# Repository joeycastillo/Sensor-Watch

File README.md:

The Sensor Watch
================

The [Sensor Watch](https://www.sensorwatch.net) is a board replacement for the classic Casio F-91W wristwatch. It is powered by a Microchip SAM L22 microcontroller with built-in segment LCD controller. You can write your own programs for the watch using the provided watch library, program the watch over USB using the built-in UF2 bootloader, and then install the board in your existing watch case to run your own software on your wrist.

Features:
* ARM Cortex M0+ microcontroller
* 32KHz crystal for real-time clock with alarm function
* Ten digit segment LCD, plus five indicator segments
* Three interrupt capable buttons
* Red / green PWM’able LED backlight
* Optional piezo buzzer (requires some light soldering)
* On-board USB Micro B connector
* Reset button with double-tap UF2 bootloader
* Nine-pin flex PCB connector

You may have noticed that there are no sensors on this board. That is by design: rather than pick sensors for you, the goal is to add a tiny flexible PCB with the sensors YOU want, and interface them over the nine-pin connector. The connector provides the following options for power and connectivity:

* 3V power (nominal voltage from a CR2016 coin cell, can drop to ~2.7V)
* An I²C interface with built-in pull-up resistors
* Five general purpose IO pins, which can be configured as:
    * Five analog inputs
    * Five interrupt-capable digital inputs, with internal pull-up or pull-down resistors
    * Five digital outputs
    * SPI controller (with one spare analog / GPIO pin leftover)
    * One UART TX/RX pair (with three GPIO leftover)
    * Up to four PWM pins on two independent TC instances
    * Two external wake inputs that can wake from the ultra-low-power BACKUP mode

| **Pin** | **Digital** | **Interrupt**   | **Analog**    | **I2C**             | **SPI**              | **UART**                 | **PWM**  | **Ext. Wake** |
| :-----: | :---------: | :-------------: | :-----------: | :-----------------: | :------------------: | :----------------------: | :------: | :-----------: |
| **A0**  | PB04        | EIC/EXTINT\[4\] | ADC/AIN\[12\] | —                   | —                    | —                        | —        | —             |
| **SCL** | —           | —               | —             | SCL<br>SERCOM1\[1\] | —                    | —                        | —        | —             |
| **SDA** | —           | —               | —             | SDA<br>SERCOM1\[0\] | —                    | —                        | —        | —             |
| **A1**  | PB01        | EIC/EXTINT\[1\] | ADC/AIN\[9\]  | —                   | SCK<br>SERCOM3\[3\]  | RX<br>SERCOM3\[3\]       | TC3\[1\] | —             |
| **A2**  | PB02        | EIC/EXTINT\[2\] | ADC/AIN\[10\] | —                   | MOSI<br>SERCOM3\[0\] | TX or RX<br>SERCOM3\[0\] | TC2\[0\] | RTC/IN\[1\]   |
| **A3**  | PB03        | EIC/EXTINT\[3\] | ADC/AIN\[11\] | —                   | CS<br>SERCOM3\[1\]   | RX<br>SERCOM3\[1\]       | TC2\[1\] | —             |
| **A4**  | PB00        | EIC/EXTINT\[0\] | ADC/AIN\[8\]  | —                   | MISO<br>SERCOM3\[2\] | TX or RX<br>SERCOM3\[2\] | TC3\[0\] | RTC/IN\[0\]   |

These tiny “sensor boards” have a set outline, and the available area for your electronics is quite small (5.7 × 5.7 × 1 mm). Still, this is plenty of room for an environmental sensor, MEMS accelerometer or magnetometer and a couple of decoupling capacitors. Note that you will likely be limited to QFN and LGA type parts; SOICs are too large, and even SSOP packages are generally too thick. You can find reference designs for several sensor boards in the `PCB/Sensor Boards` directory within this repository.

Getting code on the watch
-------------------------
The watch library in this repository is very work-in-progress, but it should allow you to get started. To create a new project, copy the “starter-project” folder in the apps folder, and write your code in the app.c file.

You will need to install [the GNU Arm Embedded Toolchain](https://developer.arm.com/tools-and-software/open-source-software/developer-tools/gnu-toolchain/gnu-rm/downloads/) to build projects for the watch. The watch library has been tested with the `9-2019-q4-major` version and the `10.3-2021.07` versions. If you're using Debian or Ubuntu, it should be sufficient to `apt install gcc-arm-none-eabi`.

To build your project, open your terminal and navigate to the project's `make` folder, then type `make`.

To install the project onto your Sensor Watch board, plug the watch into your USB port and double tap the tiny Reset button on the back of the board. You should see the LED light up red and begin pulsing. (If it does not, make sure you didn’t plug the board in upside down). Once you see the “WATCHBOOT” drive appear on your desktop, type `make install`. This will convert your compiled program to a UF2 file, and copy it over to the watch.

Using the Movement framework
----------------------------
If you just want to make minor modifications and use existing code, start with the `movement` directory. You can build the default watch firmware with:

```
cd movement/make
make
```

Then copy `movement/make/build/watch.uf2` to your watch. If you'd like to modify which faces are built, see `movement_config.h`.

You may want to test out changes in the emulator first. To do this, you'll need to install [emscripten](https://emscripten.org/), then run:

```
cd movement/make
emmake make
python3 -m http.server -d build-sim
```

Finally, visit [watch.html](http://localhost:8000/watch.html) to see your work.

Hardware Schematics and PCBs
----------------------------

| Name | Color | Schematic | Gerbers |
| ---- | ----- | --------- | ------- |
| Sensorwatch Lite | RED   | [PCB/Main Boards/OSO-SWAT-B1](PCB/Main%20Boards/OSO-SWAT-B1) | [OSO-SWAT-B1-03](PCB/Main%20Boards/OSO-SWAT-B1/OSO-SWAT-B1-03.zip) |
| Sensorwatch      | GREEN | [OSO-SWAT-A1-05](PCB/Main%20Boards/OSO-SWAT-A1/OSO-SWAT-A1-05.sch) (Eagle format) | ? |
| Sensorwatch Pro  | TBD   | TBD  | TBD |

License
-------
Different components of the project are licensed differently, see [LICENSE.md](https://github.com/joeycastillo/Sensor-Watch/blob/main/LICENSE.md).

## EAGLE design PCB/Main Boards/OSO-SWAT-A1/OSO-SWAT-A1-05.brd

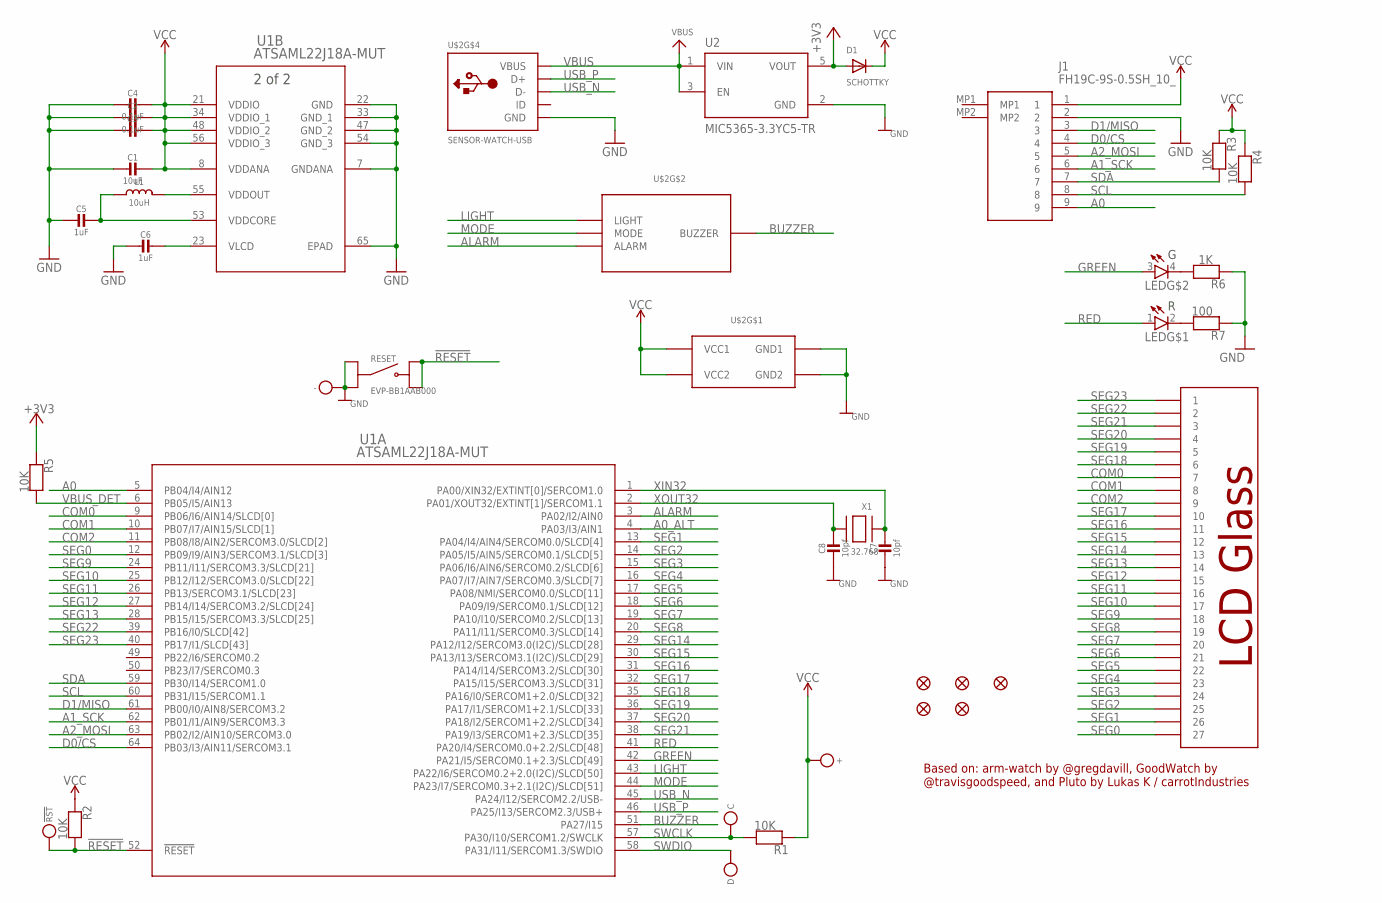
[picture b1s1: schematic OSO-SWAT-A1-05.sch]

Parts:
!RST: MICROBUILDER_TESTPOINTROUND1.5MM; MICROBUILDER_TESTPOINT_ROUND_1.5MM
+: MICROBUILDER_TESTPOINTROUND1.5MM; MICROBUILDER_TESTPOINT_ROUND_1.5MM
-: MICROBUILDER_TESTPOINTROUND1.5MM; MICROBUILDER_TESTPOINT_ROUND_1.5MM
C: MICROBUILDER_TESTPOINTROUND1.5MM; MICROBUILDER_TESTPOINT_ROUND_1.5MM
C1: 10uF; _0603MP
C2, C3, C4: 0.1uF; _0603MP
C5, C6: 1uF; _0603MP
C7, C8: 10pf; _0402MP
D: MICROBUILDER_TESTPOINTROUND1.5MM; MICROBUILDER_TESTPOINT_ROUND_1.5MM
D1: SCHOTTKY; SOD-323F
FID1, FID2, FID3, FID4, FID6: FIDUCIAL_1MM
J1: FH19C-9S-0.5SH_10_; FH19C9S05SH10
L1: 10uH; MICROBUILDER__0805MP
LED: QBLP655-RIG; LED_QBLP655
R1, R2, R3, R4, R5: 10K; _0603MP
R6: 1K; _0603MP
R7: 100; _0603MP
RESET: EVP-BB1AAB000; SW_EVP-BB1AAB000
U1: ATSAML22J18A-MUT; QFN64_9X9MC_MCH
U2: MIC5365-3.3YC5-TR; SOT65P210X110-5N
U$2: SENSOR-WATCH-USB; CASIO-F91W-OUTLINE-USB
X1: 32.768; XTAL3215

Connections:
!RESET: !RST.P$1, R2.2, RESET.B1, RESET.B2, U1.52 (!RESET)
+3V3: D1.A, R5.1, U2.5 (VOUT)
A0: J1.9, U1.5 (PB04/I4/AIN12)
A0_ALT: U1.4 (PA03/I3/AIN1)
A1_SCK: J1.6, U1.62 (PB01/I1/AIN9/SERCOM3.3)
A2_MOSI: J1.5, U1.63 (PB02/I2/AIN10/SERCOM3.0)
ALARM: U1.3 (PA02/I2/AIN0), U$2.ALARM
BUZZER: U1.51 (PA27/I15), U$2.BUZZER
COM0: U1.9 (PB06/I6/AIN14/SLCD[0]), U$2.7
COM1: U1.10 (PB07/I7/AIN15/SLCD[1]), U$2.8
COM2: U1.11 (PB08/I8/AIN2/SERCOM3.0/SLCD[2]), U$2.9
D0/CS: J1.4, U1.64 (PB03/I3/AIN11/SERCOM3.1)
D1/MISO: J1.3, U1.61 (PB00/I0/AIN8/SERCOM3.2)
GND: -.P$1, C1.2, C2.2, C3.2, C4.2, C5.2, C6.2, C7.2, C8.2, J1.2, R6.1, R7.1, RESET.A1, RESET.A2, U1.7 (GNDANA), U1.22 (GND), U1.33 (GND_1), U1.47 (GND_2), U1.54 (GND_3), U1.65 (EPAD), U2.2 (GND), U$2.GND, U$2.GND1, U$2.GND2
GREEN: LED.3 (A), U1.42 (PA21/I5/SERCOM0.1+2.3/SLCD[49])
LIGHT: U1.43 (PA22/I6/SERCOM0.2+2.0(I2C)/SLCD[50]), U$2.LIGHT
MODE: U1.44 (PA23/I7/SERCOM0.3+2.1(I2C)/SLCD[51]), U$2.MODE
unnamed: LED.4 (C), R6.2
unnamed: LED.2 (C), R7.2
RED: LED.1 (A), U1.41 (PA20/I4/SERCOM0.0+2.2/SLCD[48])
SCL: J1.8, R4.2, U1.60 (PB31/I15/SERCOM1.1)
SDA: J1.7, R3.2, U1.59 (PB30/I14/SERCOM1.0)
SEG0: U1.12 (PB09/I9/AIN3/SERCOM3.1/SLCD[3]), U$2.27
SEG1: U1.13 (PA04/I4/AIN4/SERCOM0.0/SLCD[4]), U$2.26
SEG2: U1.14 (PA05/I5/AIN5/SERCOM0.1/SLCD[5]), U$2.25
SEG3: U1.15 (PA06/I6/AIN6/SERCOM0.2/SLCD[6]), U$2.24
SEG4: U1.16 (PA07/I7/AIN7/SERCOM0.3/SLCD[7]), U$2.23
SEG5: U1.17 (PA08/NMI/SERCOM0.0/SLCD[11]), U$2.22
SEG6: U1.18 (PA09/I9/SERCOM0.1/SLCD[12]), U$2.21
SEG7: U1.19 (PA10/I10/SERCOM0.2/SLCD[13]), U$2.20
SEG8: U1.20 (PA11/I11/SERCOM0.3/SLCD[14]), U$2.19
SEG9: U1.24 (PB11/I11/SERCOM3.3/SLCD[21]), U$2.18
SEG10: U1.25 (PB12/I12/SERCOM3.0/SLCD[22]), U$2.17
SEG11: U1.26 (PB13/SERCOM3.1/SLCD[23]), U$2.16
SEG12: U1.27 (PB14/I14/SERCOM3.2/SLCD[24]), U$2.15
SEG13: U1.28 (PB15/I15/SERCOM3.3/SLCD[25]), U$2.14
SEG14: U1.29 (PA12/I12/SERCOM3.0(I2C)/SLCD[28]), U$2.13
SEG15: U1.30 (PA13/I13/SERCOM3.1(I2C)/SLCD[29]), U$2.12
SEG16: U1.31 (PA14/I14/SERCOM3.2/SLCD[30]), U$2.11
SEG17: U1.32 (PA15/I15/SERCOM3.3/SLCD[31]), U$2.10
SEG18: U1.35 (PA16/I0/SERCOM1+2.0/SLCD[32]), U$2.6
SEG19: U1.36 (PA17/I1/SERCOM1+2.1/SLCD[33]), U$2.5
SEG20: U1.37 (PA18/I2/SERCOM1+2.2/SLCD[34]), U$2.4
SEG21: U1.38 (PA19/I3/SERCOM1+2.3/SLCD[35]), U$2.3
SEG22: U1.39 (PB16/I0/SLCD[42]), U$2.2
SEG23: U1.40 (PB17/I1/SLCD[43]), U$2.1
SWCLK: C.P$1, R1.2, U1.57 (PA30/I10/SERCOM1.2/SWCLK)
SWDIO: D.P$1, U1.58 (PA31/I11/SERCOM1.3/SWDIO)
USB_N: U1.45 (PA24/I12/SERCOM2.2/USB-), U$2.USB_N (D-)
USB_P: U1.46 (PA25/I13/SERCOM2.3/USB+), U$2.USB_P (D+)
VBUS: U2.1 (VIN), U2.3 (EN), U$2.VBUS
VBUS_DET: R5.2, U1.6 (PB05/I5/AIN13)
VCC: +.P$1, C1.1, C2.1, C3.1, C4.1, D1.C, J1.1, R1.1, R2.1, R3.1, R4.1, U1.8 (VDDANA), U1.21 (VDDIO), U1.34 (VDDIO_1), U1.48 (VDDIO_2), U1.56 (VDDIO_3), U$2.VCC1, U$2.VCC2
VDDCORE: C5.1, L1.1, U1.53 (VDDCORE)
VDDOUT: L1.2, U1.55 (VDDOUT)
VLCD: C6.1, U1.23 (VLCD)
XIN32: C7.1, U1.1 (PA00/XIN32/EXTINT[0]/SERCOM1.0), X1.P$1
XOUT32: C8.1, U1.2 (PA01/XOUT32/EXTINT[1]/SERCOM1.1), X1.P$2

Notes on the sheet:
Based on: arm-watch by @gregdavill, GoodWatch by @travisgoodspeed, and Pluto by Lukas K / carrotIndustries

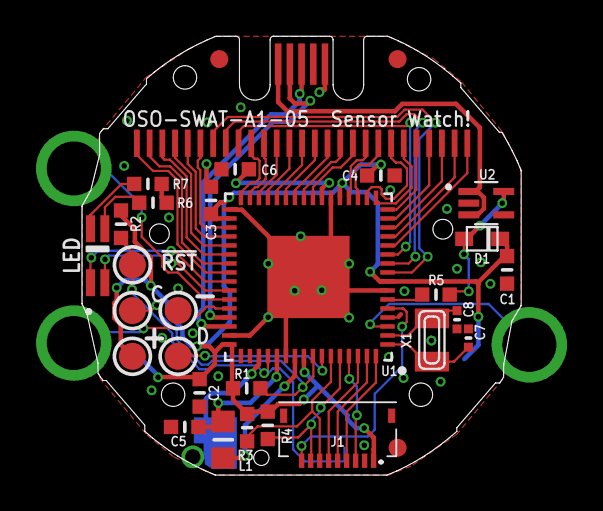
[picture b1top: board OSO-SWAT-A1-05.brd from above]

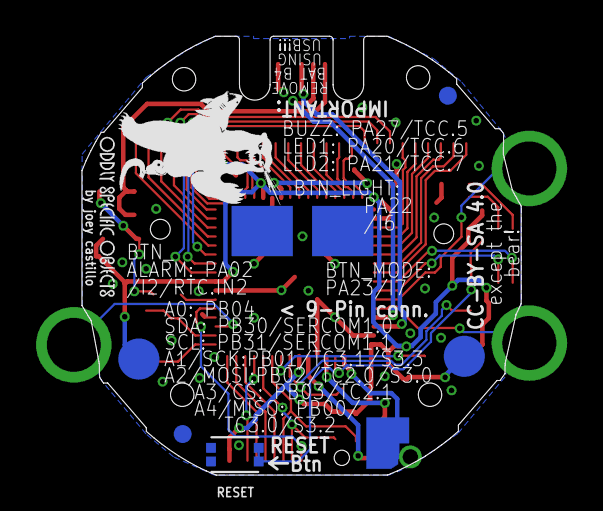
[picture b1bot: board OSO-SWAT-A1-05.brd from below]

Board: 2 copper layers, 24.4 x 24.4 mm, 36 parts (5 on the bottom side), 57 nets.

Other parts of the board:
U$5: OSO_BEAR_250X360MIL_1000DPI
U$6: OSO_WORDMARK_ONELINE_350MIL_1000DPI

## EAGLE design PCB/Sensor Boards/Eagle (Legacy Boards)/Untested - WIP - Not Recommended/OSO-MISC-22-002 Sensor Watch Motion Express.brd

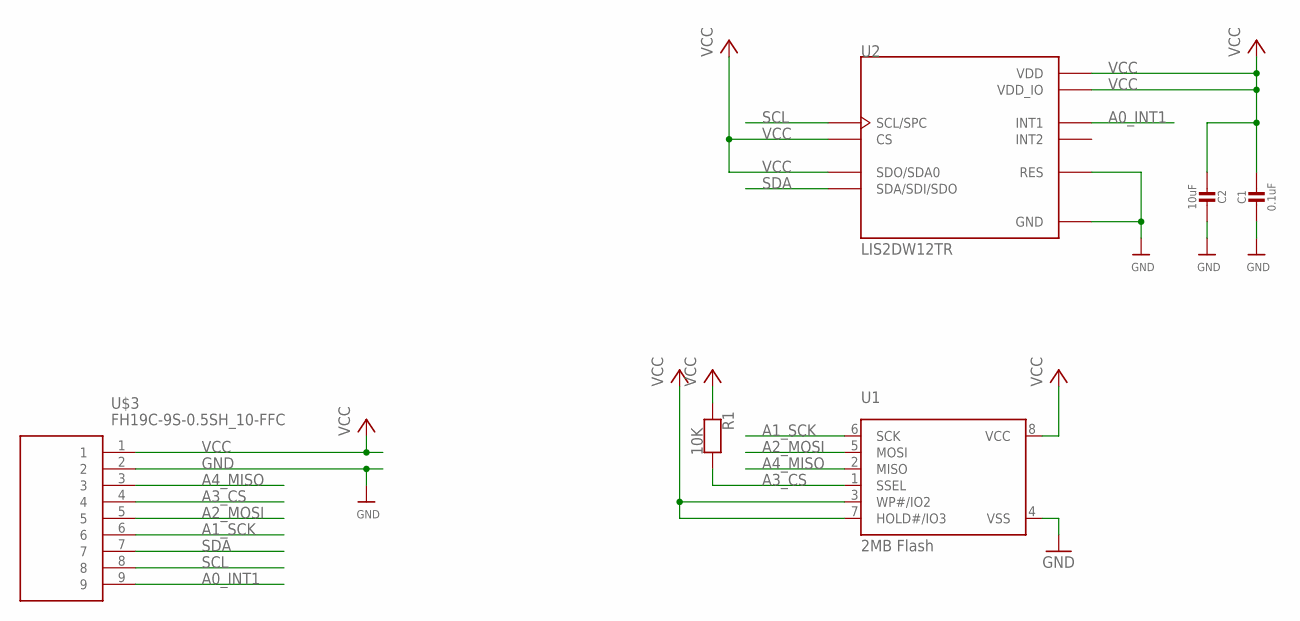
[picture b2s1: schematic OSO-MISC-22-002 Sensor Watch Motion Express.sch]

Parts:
C1: 0.1uF; _0603MP
C2: 10uF; _0603MP
R1: 10K; _0603MP
U1: 2MB Flash; USON8
U2: LIS2DW12TR; LGA12R50P4X4_200X200X70
U$3: FH19C-9S-0.5SH_10-FFC; FH19C9S05SH10-FFC

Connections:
A0_INT1: U2.12 (INT1), U$3.9
A1_SCK: U1.6 (SCK), U$3.6
A2_MOSI: U1.5 (MOSI), U$3.5
A3_CS: R1.2, U1.1 (SSEL), U$3.4
A4_MISO: U1.2 (MISO), U$3.3
GND: C1.2, C2.1, U1.4 (VSS), U2.6 (GND), U2.7 (RES), U2.8 (GND), U$3.2
SCL: U2.1 (SCL/SPC), U$3.8
SDA: U2.4 (SDA/SDI/SDO), U$3.7
VCC: C1.1, C2.2, R1.1, U1.3 (WP#/IO2), U1.7 (HOLD#/IO3), U1.8 (VCC), U2.2 (CS), U2.3 (SDO/SDA0), U2.9 (VDD), U2.10 (VDD_IO), U$3.1

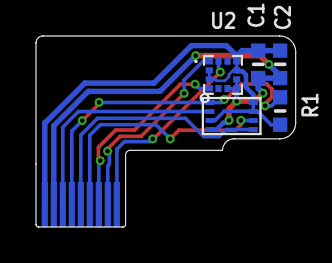
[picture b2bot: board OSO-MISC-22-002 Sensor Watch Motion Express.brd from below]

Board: 2 copper layers, 14.4 x 10.6 mm, 6 parts (5 on the bottom side), 9 nets.

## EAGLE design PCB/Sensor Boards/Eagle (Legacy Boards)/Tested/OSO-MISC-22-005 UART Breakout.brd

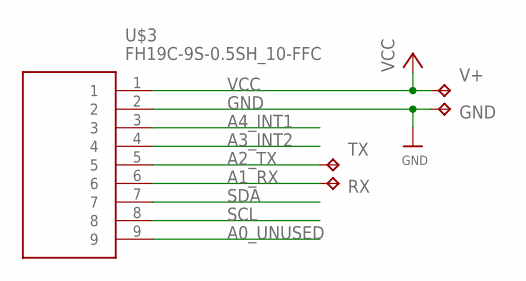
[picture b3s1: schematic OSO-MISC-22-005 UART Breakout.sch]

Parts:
GND: TPTP20R; TP20R
RX: TPTP20R; TP20R
TX: TPTP20R; TP20R
U$3: FH19C-9S-0.5SH_10-FFC; FH19C9S05SH10-FFC
V+: TPTP20R; TP20R

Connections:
A0_UNUSED: U$3.9
A1_RX: RX.TP, U$3.6
A2_TX: TX.TP, U$3.5
A3_INT2: U$3.4
A4_INT1: U$3.3
GND: GND.TP, U$3.2
SCL: U$3.8
SDA: U$3.7
VCC: U$3.1, V+.TP

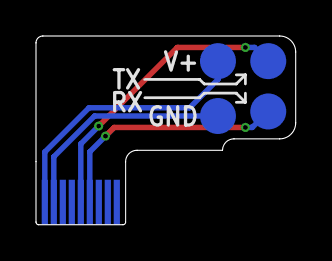
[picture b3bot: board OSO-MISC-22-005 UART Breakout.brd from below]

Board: 2 copper layers, 14.4 x 10.5 mm, 5 parts (4 on the bottom side), 4 nets.

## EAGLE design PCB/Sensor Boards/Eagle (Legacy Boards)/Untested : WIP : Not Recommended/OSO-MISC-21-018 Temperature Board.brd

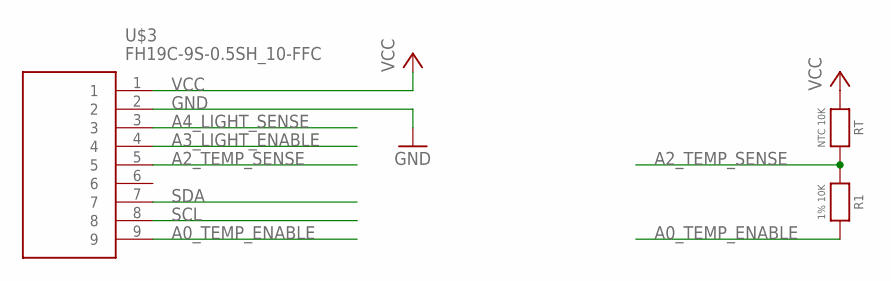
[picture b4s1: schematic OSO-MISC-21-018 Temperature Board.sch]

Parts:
R1: 1% 10K; _0603MP
RT: NTC 10K; _0603
U$3: FH19C-9S-0.5SH_10-FFC; FH19C9S05SH10-FFC

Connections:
A0_TEMP_ENABLE: R1.2, U$3.9
A2_TEMP_SENSE: R1.1, RT.2, U$3.5
A3_LIGHT_ENABLE: U$3.4
A4_LIGHT_SENSE: U$3.3
GND: U$3.2
SCL: U$3.8
SDA: U$3.7
VCC: RT.1, U$3.1

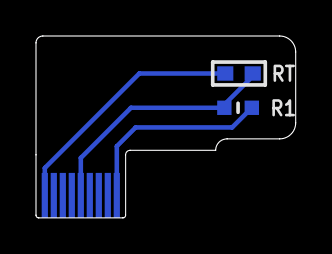
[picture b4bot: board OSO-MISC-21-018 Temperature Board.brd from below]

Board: 2 copper layers, 14.4 x 10.1 mm, 3 parts (2 on the bottom side), 3 nets.

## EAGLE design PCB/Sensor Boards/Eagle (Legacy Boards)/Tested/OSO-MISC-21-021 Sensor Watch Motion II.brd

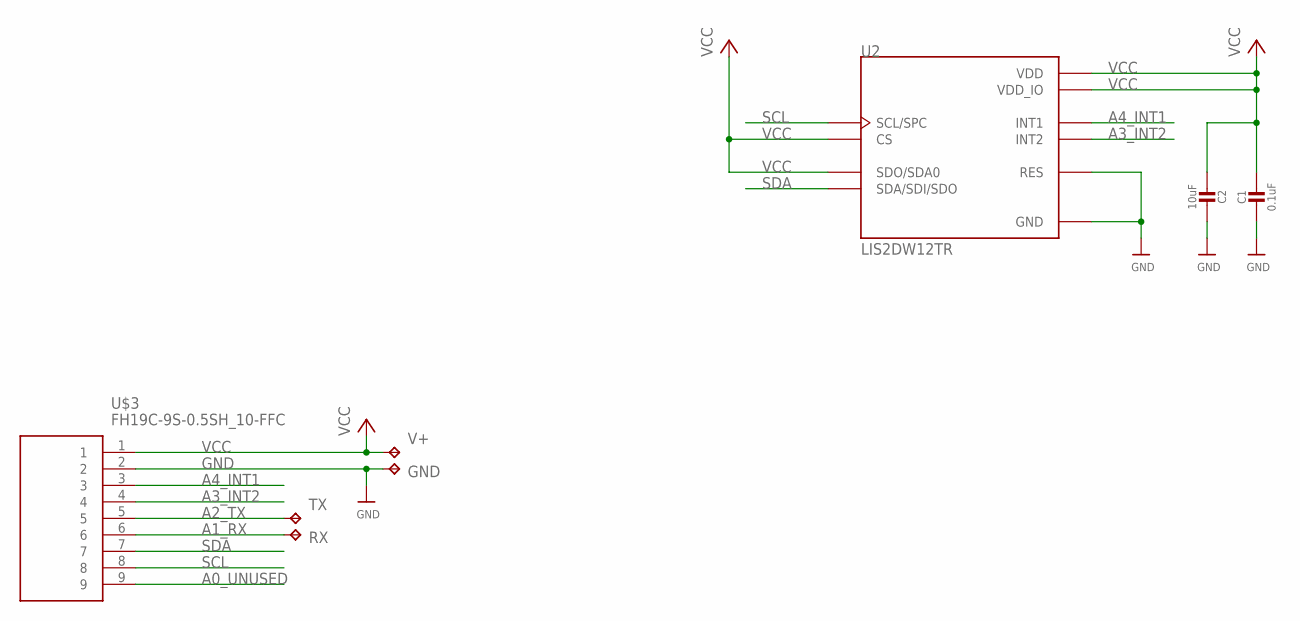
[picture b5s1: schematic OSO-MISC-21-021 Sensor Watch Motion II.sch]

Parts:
C1: 0.1uF; _0603MP
C2: 10uF; _0603MP
GND: TPB1,27; B1,27
RX: TPB1,27; B1,27
TX: TPB1,27; B1,27
U2: LIS2DW12TR; LGA12R50P4X4_200X200X70
U$3: FH19C-9S-0.5SH_10-FFC; FH19C9S05SH10-FFC
V+: TPB1,27; B1,27

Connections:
A0_UNUSED: U$3.9
A1_RX: RX.TP, U$3.6
A2_TX: TX.TP, U$3.5
A3_INT2: U2.11 (INT2), U$3.4
A4_INT1: U2.12 (INT1), U$3.3
GND: C1.2, C2.1, GND.TP, U2.6 (GND), U2.7 (RES), U2.8 (GND), U$3.2
SCL: U2.1 (SCL/SPC), U$3.8
SDA: U2.4 (SDA/SDI/SDO), U$3.7
VCC: C1.1, C2.2, U2.2 (CS), U2.3 (SDO/SDA0), U2.9 (VDD), U2.10 (VDD_IO), U$3.1, V+.TP

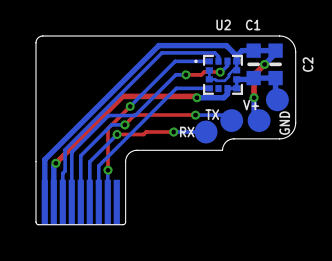
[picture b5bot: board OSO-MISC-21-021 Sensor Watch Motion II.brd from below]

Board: 2 copper layers, 14.4 x 10.5 mm, 8 parts (7 on the bottom side), 8 nets.

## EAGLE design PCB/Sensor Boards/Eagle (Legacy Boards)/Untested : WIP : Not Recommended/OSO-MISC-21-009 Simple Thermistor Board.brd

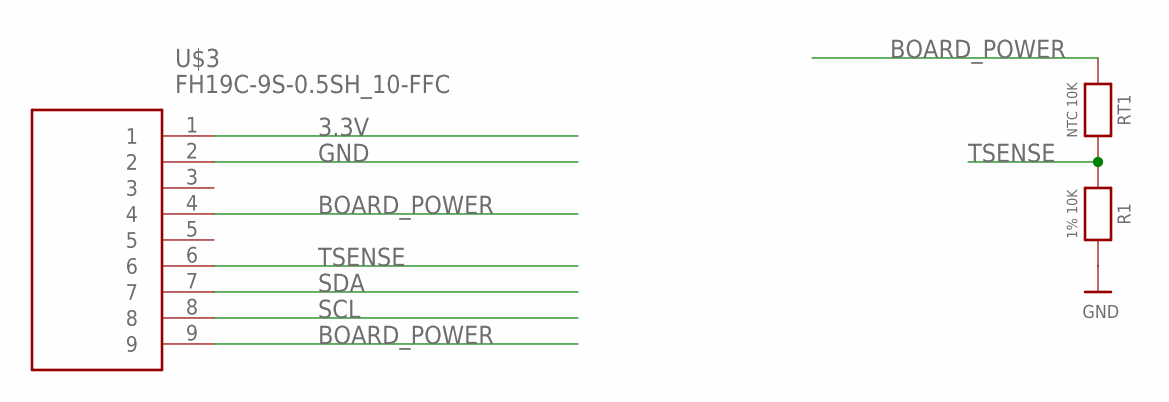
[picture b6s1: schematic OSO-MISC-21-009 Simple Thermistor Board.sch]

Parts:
R1: 1% 10K; _1206
RT1: NTC 10K; _1206
U$3: FH19C-9S-0.5SH_10-FFC; FH19C9S05SH10-FFC

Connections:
3.3V: U$3.1
BOARD_POWER: RT1.1, U$3.4, U$3.9
GND: R1.2, U$3.2
SCL: U$3.8
SDA: U$3.7
TSENSE: R1.1, RT1.2, U$3.6

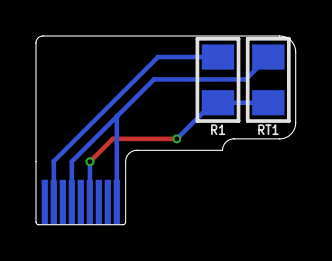
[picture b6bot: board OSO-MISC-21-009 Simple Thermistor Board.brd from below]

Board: 2 copper layers, 14.4 x 10.5 mm, 3 parts (2 on the bottom side), 3 nets.

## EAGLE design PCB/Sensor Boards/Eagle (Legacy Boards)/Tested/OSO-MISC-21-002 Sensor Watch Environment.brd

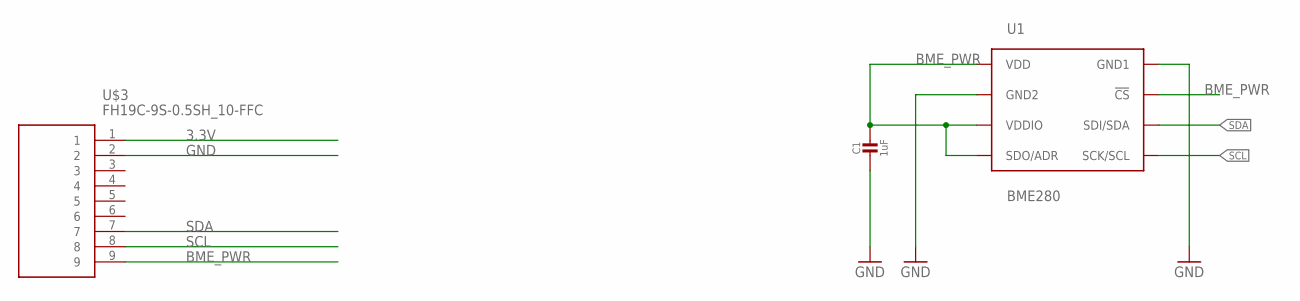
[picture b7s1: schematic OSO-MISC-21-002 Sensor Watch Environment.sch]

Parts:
C1: 1uF; _0603MP
U1: BME280; BME280_LGA
U$3: FH19C-9S-0.5SH_10-FFC; FH19C9S05SH10-FFC

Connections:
3.3V: U$3.1
BME_PWR: C1.1, U1.P$2 (!CS), U1.P$5 (SDO/ADR), U1.P$6 (VDDIO), U1.P$8 (VDD), U$3.9
GND: C1.2, U1.P$1 (GND1), U1.P$7 (GND2), U$3.2
SCL: U1.P$4 (SCK/SCL), U$3.8
SDA: U1.P$3 (SDI/SDA), U$3.7

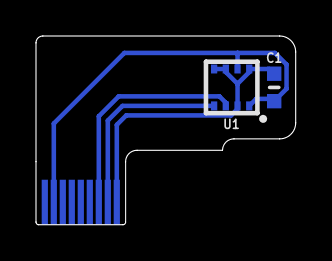
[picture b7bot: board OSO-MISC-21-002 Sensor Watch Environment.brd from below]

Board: 2 copper layers, 14.4 x 10.5 mm, 3 parts (2 on the bottom side), 4 nets.

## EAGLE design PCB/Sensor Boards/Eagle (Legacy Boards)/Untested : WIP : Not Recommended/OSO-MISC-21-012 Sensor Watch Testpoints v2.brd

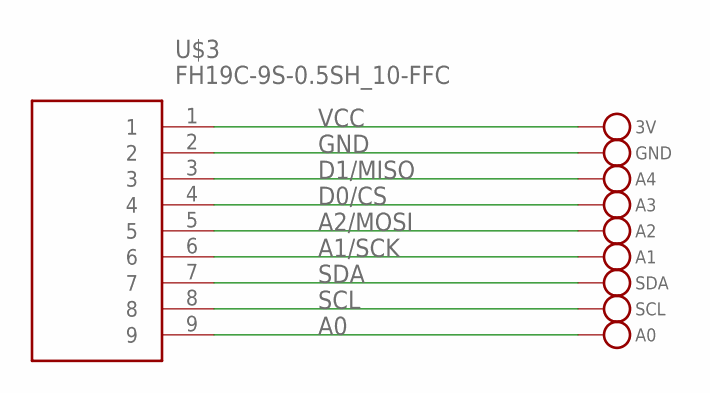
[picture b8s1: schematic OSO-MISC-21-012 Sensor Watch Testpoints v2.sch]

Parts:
3V: MICROBUILDER_TESTPOINT1.5X2.0MM_NOCREAM; MICROBUILDER_PAD-1.5X2.0
A0, A1, A2, A3, A4: MICROBUILDER_TESTPOINT1.5X2.0MM_NOCREAM; MICROBUILDER_PAD-1.5X2.0
GND: MICROBUILDER_TESTPOINT1.5X2.0MM_NOCREAM; MICROBUILDER_PAD-1.5X2.0
SCL: MICROBUILDER_TESTPOINT1.5X2.0MM_NOCREAM; MICROBUILDER_PAD-1.5X2.0
SDA: MICROBUILDER_TESTPOINT1.5X2.0MM_NOCREAM; MICROBUILDER_PAD-1.5X2.0
U$3: FH19C-9S-0.5SH_10-FFC; FH19C9S05SH10-FFC

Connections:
A0: A0.P$1, U$3.9
A1/SCK: A1.P$1, U$3.6
A2/MOSI: A2.P$1, U$3.5
D0/CS: A3.P$1, U$3.4
D1/MISO: A4.P$1, U$3.3
GND: GND.P$1, U$3.2
SCL: SCL.P$1, U$3.8
SDA: SDA.P$1, U$3.7
VCC: 3V.P$1, U$3.1

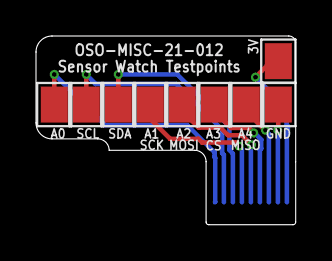
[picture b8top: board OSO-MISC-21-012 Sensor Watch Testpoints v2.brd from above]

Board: 2 copper layers, 14.4 x 10.5 mm, 10 parts (0 on the bottom side), 9 nets.

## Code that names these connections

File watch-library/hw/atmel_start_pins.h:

/*
 * Code generated from Atmel Start.
 *
 * This file will be overwritten when reconfiguring your Atmel Start project.
 * Please copy examples or other code you want to keep to a separate file
 * to avoid losing it when reconfiguring.
 */
#ifndef ATMEL_START_PINS_H_INCLUDED
#define ATMEL_START_PINS_H_INCLUDED

#include <hal_gpio.h>

// SAML22 has 9 pin functions

#define GPIO_PIN_FUNCTION_A 0
#define GPIO_PIN_FUNCTION_B 1
#define GPIO_PIN_FUNCTION_C 2
#define GPIO_PIN_FUNCTION_D 3
#define GPIO_PIN_FUNCTION_E 4
#define GPIO_PIN_FUNCTION_F 5
#define GPIO_PIN_FUNCTION_G 6
#define GPIO_PIN_FUNCTION_H 7
#define GPIO_PIN_FUNCTION_I 8

#define VBUS_DET GPIO(GPIO_PORTA, 3)
#define SEG1 GPIO(GPIO_PORTA, 4)
#define SEG2 GPIO(GPIO_PORTA, 5)
#define SEG3 GPIO(GPIO_PORTA, 6)
#define SEG4 GPIO(GPIO_PORTA, 7)
#define SEG5 GPIO(GPIO_PORTA, 8)
#define SEG6 GPIO(GPIO_PORTA, 9)
#define SEG7 GPIO(GPIO_PORTA, 10)
#define SEG8 GPIO(GPIO_PORTA, 11)
#define SEG14 GPIO(GPIO_PORTA, 12)
#define SEG15 GPIO(GPIO_PORTA, 13)
#define SEG16 GPIO(GPIO_PORTA, 14)
#define SEG17 GPIO(GPIO_PORTA, 15)
#define SEG18 GPIO(GPIO_PORTA, 16)
#define SEG19 GPIO(GPIO_PORTA, 17)
#define SEG20 GPIO(GPIO_PORTA, 18)
#define SEG21 GPIO(GPIO_PORTA, 19)
#ifdef WATCH_SWAP_LED_PINS
    #define RED GPIO(GPIO_PORTA, 21)
    #define GREEN GPIO(GPIO_PORTA, 20)
#else
    #define RED GPIO(GPIO_PORTA, 20)
    #define GREEN GPIO(GPIO_PORTA, 21)
#endif
#define BTN_ALARM GPIO(GPIO_PORTA, 2)
#define BTN_LIGHT GPIO(GPIO_PORTA, 22)
#define BTN_MODE GPIO(GPIO_PORTA, 23)
#define BUZZER GPIO(GPIO_PORTA, 27)
#define A0 GPIO(GPIO_PORTB, 4)
#define A1 GPIO(GPIO_PORTB, 1)
#define A2 GPIO(GPIO_PORTB, 2)
#define A3 GPIO(GPIO_PORTB, 3)
#define A4 GPIO(GPIO_PORTB, 0)
#define D0 GPIO(GPIO_PORTB, 3)
#define D1 GPIO(GPIO_PORTB, 0)
#define COM0 GPIO(GPIO_PORTB, 6)
#define COM1 GPIO(GPIO_PORTB, 7)
#define COM2 GPIO(GPIO_PORTB, 8)
#define SEG0 GPIO(GPIO_PORTB, 9)
#define SEG9 GPIO(GPIO_PORTB, 11)
#define SEG10 GPIO(GPIO_PORTB, 12)
#define SEG11 GPIO(GPIO_PORTB, 13)
#define SEG12 GPIO(GPIO_PORTB, 14)
#define SEG13 GPIO(GPIO_PORTB, 15)
#define SEG22 GPIO(GPIO_PORTB, 16)
#define SEG23 GPIO(GPIO_PORTB, 17)
#define SDA GPIO(GPIO_PORTB, 30)
#define SCL GPIO(GPIO_PORTB, 31)

#endif // ATMEL_START_PINS_H_INCLUDED

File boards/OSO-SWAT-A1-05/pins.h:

#ifndef PINS_H_INCLUDED
#define PINS_H_INCLUDED

// Detects if we are on USB power.
#define VBUS_DET GPIO(GPIO_PORTB, 5)

// Buttons
#define BTN_ALARM GPIO(GPIO_PORTA, 2)
#define WATCH_BTN_ALARM_EIC_CHANNEL 2
#define BTN_LIGHT GPIO(GPIO_PORTA, 22)
#define WATCH_BTN_LIGHT_EIC_CHANNEL 6
#define BTN_MODE GPIO(GPIO_PORTA, 23)
#define WATCH_BTN_MODE_EIC_CHANNEL 7

// Buzzer
#define BUZZER GPIO(GPIO_PORTA, 27)
#define WATCH_BUZZER_TCC_PINMUX PINMUX_PA27F_TCC0_WO5
#define WATCH_BUZZER_TCC_CHANNEL 1

// LEDs
#ifdef WATCH_IS_BLUE_BOARD
    #define RED GPIO(GPIO_PORTA, 21)
    #define WATCH_RED_TCC_PINMUX PINMUX_PA21F_TCC0_WO7
    #define WATCH_RED_TCC_CHANNEL 3
    #define GREEN GPIO(GPIO_PORTA, 20)
    #define WATCH_GREEN_TCC_CHANNEL 2
    #define WATCH_GREEN_TCC_PINMUX PINMUX_PA20F_TCC0_WO6
#else
    #define RED GPIO(GPIO_PORTA, 20)
    #define WATCH_RED_TCC_PINMUX PINMUX_PA20F_TCC0_WO6
    #define WATCH_RED_TCC_CHANNEL 2
    #define GREEN GPIO(GPIO_PORTA, 21)
    #define WATCH_GREEN_TCC_CHANNEL 3
    #define WATCH_GREEN_TCC_PINMUX PINMUX_PA21F_TCC0_WO7
#endif

// Segment LCD
#define SLCD0 GPIO(GPIO_PORTB, 6)
#define SLCD1 GPIO(GPIO_PORTB, 7)
#define SLCD2 GPIO(GPIO_PORTB, 8)
#define SLCD3 GPIO(GPIO_PORTB, 9)
#define SLCD4 GPIO(GPIO_PORTA, 4)
#define SLCD5 GPIO(GPIO_PORTA, 5)
#define SLCD6 GPIO(GPIO_PORTA, 6)
#define SLCD7 GPIO(GPIO_PORTA, 7)
#define SLCD8 GPIO(GPIO_PORTA, 8)
#define SLCD9 GPIO(GPIO_PORTA, 9)
#define SLCD10 GPIO(GPIO_PORTA, 10)
#define SLCD11 GPIO(GPIO_PORTA, 11)
#define SLCD12 GPIO(GPIO_PORTB, 11)
#define SLCD13 GPIO(GPIO_PORTB, 12)
#define SLCD14 GPIO(GPIO_PORTB, 13)
#define SLCD15 GPIO(GPIO_PORTB, 14)
#define SLCD16 GPIO(GPIO_PORTB, 15)
#define SLCD17 GPIO(GPIO_PORTA, 12)
#define SLCD18 GPIO(GPIO_PORTA, 13)
#define SLCD19 GPIO(GPIO_PORTA, 14)
#define SLCD20 GPIO(GPIO_PORTA, 15)
#define SLCD21 GPIO(GPIO_PORTA, 16)
#define SLCD22 GPIO(GPIO_PORTA, 17)
#define SLCD23 GPIO(GPIO_PORTA, 18)
#define SLCD24 GPIO(GPIO_PORTA, 19)
#define SLCD25 GPIO(GPIO_PORTB, 16)
#define SLCD26 GPIO(GPIO_PORTB, 17)

// 9-pin connector
#define A0 GPIO(GPIO_PORTB, 4)
#define WATCH_A0_EIC_CHANNEL 4
#define A1 GPIO(GPIO_PORTB, 1)
#define WATCH_A1_EIC_CHANNEL 1
#define A2 GPIO(GPIO_PORTB, 2)
#define WATCH_A2_EIC_CHANNEL 2
#define A3 GPIO(GPIO_PORTB, 3)
#define WATCH_A3_EIC_CHANNEL 3
#define A4 GPIO(GPIO_PORTB, 0)
#define WATCH_A4_EIC_CHANNEL 0
#define SDA GPIO(GPIO_PORTB, 30)
#define SCL GPIO(GPIO_PORTB, 31)

// aliases for as A3/A4; these were mentioned as D0/D1 in early documentation.
#define D0 GPIO(GPIO_PORTB, 3)
#define D1 GPIO(GPIO_PORTB, 0)

// interrupt mapping
#define EXT_IRQ_AMOUNT 6
#define CONFIG_EIC_EXTINT_MAP {0, PIN_PB00}, {1, PIN_PB01}, {2, PIN_PA02}, {3, PIN_PB03}, {6, PIN_PA22}, {7, PIN_PA23},

#endif // PINS_H_INCLUDED

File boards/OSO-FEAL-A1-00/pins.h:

#ifndef PINS_H_INCLUDED
#define PINS_H_INCLUDED

// Detects if we are on USB power.
#define VBUS_DET GPIO(GPIO_PORTA, 3)

// Buttons
#define BTN_ALARM GPIO(GPIO_PORTA, 2)
#define WATCH_BTN_ALARM_EIC_CHANNEL 2
#define BTN_LIGHT GPIO(GPIO_PORTB, 5)
#define WATCH_BTN_LIGHT_EIC_CHANNEL 5
#define BTN_MODE GPIO(GPIO_PORTA, 7)
#define WATCH_BTN_MODE_EIC_CHANNEL 7

// Buzzer
#define BUZZER GPIO(GPIO_PORTA, 27)
#define WATCH_BUZZER_TCC_PINMUX PINMUX_PA27F_TCC0_WO5
#define WATCH_BUZZER_TCC_CHANNEL 1

// LEDs
#define WATCH_INVERT_LED_POLARITY
#define RED GPIO(GPIO_PORTA, 4)
#define WATCH_RED_TCC_CHANNEL 0
#define WATCH_RED_TCC_PINMUX PINMUX_PA04E_TCC0_WO0

#ifdef WATCH_IS_BLUE_BOARD
    #define GREEN GPIO(GPIO_PORTB, 22)
    #define WATCH_GREEN_TCC_CHANNEL 2
    #define WATCH_GREEN_TCC_PINMUX PINMUX_PB22F_TCC0_WO2
#else
    #define GREEN GPIO(GPIO_PORTB, 23)
    #define WATCH_GREEN_TCC_CHANNEL 3
    #define WATCH_GREEN_TCC_PINMUX PINMUX_PB23F_TCC0_WO3
#endif


// Segment LCD
// The LCD in this board can run comfortably at a lower voltage.
#define CONF_SLCD_CONTRAST_ADJUST 7

#define SLCD0 GPIO(GPIO_PORTB, 6)
#define SLCD1 GPIO(GPIO_PORTB, 7)
#define SLCD2 GPIO(GPIO_PORTB, 8)
#define SLCD3 GPIO(GPIO_PORTB, 9)
#define SLCD4 GPIO(GPIO_PORTA, 5)
#define SLCD5 GPIO(GPIO_PORTA, 6)
#define SLCD6 GPIO(GPIO_PORTA, 8)
#define SLCD7 GPIO(GPIO_PORTA, 9)
#define SLCD8 GPIO(GPIO_PORTA, 10)
#define SLCD9 GPIO(GPIO_PORTA, 11)
#define SLCD10 GPIO(GPIO_PORTB, 11)
#define SLCD11 GPIO(GPIO_PORTB, 12)
#define SLCD12 GPIO(GPIO_PORTB, 13)
#define SLCD13 GPIO(GPIO_PORTB, 14)
#define SLCD14 GPIO(GPIO_PORTB, 15)
#define SLCD15 GPIO(GPIO_PORTA, 14)
#define SLCD16 GPIO(GPIO_PORTA, 15)
#define SLCD17 GPIO(GPIO_PORTA, 16)
#define SLCD18 GPIO(GPIO_PORTA, 17)
#define SLCD19 GPIO(GPIO_PORTA, 18)
#define SLCD20 GPIO(GPIO_PORTA, 19)
#define SLCD21 GPIO(GPIO_PORTB, 16)
#define SLCD22 GPIO(GPIO_PORTB, 17)
#define SLCD23 GPIO(GPIO_PORTA, 20)
#define SLCD24 GPIO(GPIO_PORTA, 21)
#define SLCD25 GPIO(GPIO_PORTA, 22)
#define SLCD26 GPIO(GPIO_PORTA, 23)
// This board uses a slightly different pin mapping from the standard watch, and it's not enough to
// just declare the pins. We also have to set the LCD Pin Enable register with the SLCD pins we're
// using. These numbers are not port/pin numbers, but the "SLCD/LP[x]" numbers in the pinmux table.
// If not defined in pins.h, the LCD driver will fall back to the pin mapping in hpl_slcd_config.h.
// LPENL is for pins SLCD/LP[0..31].
#define CONF_SLCD_LPENL (\
        (uint32_t)1 <<  0 | \
        (uint32_t)1 <<  1 | \
        (uint32_t)1 <<  2 | \
        (uint32_t)1 <<  3 | \
        (uint32_t)1 <<  5 | \
        (uint32_t)1 <<  6 | \
        (uint32_t)1 << 11 | \
        (uint32_t)1 << 12 | \
        (uint32_t)1 << 13 | \
        (uint32_t)1 << 14 | \
        (uint32_t)1 << 21 | \
        (uint32_t)1 << 22 | \
        (uint32_t)1 << 23 | \
        (uint32_t)1 << 24 | \
        (uint32_t)1 << 25 | \
        (uint32_t)1 << 30 | \
        (uint32_t)1 << 31 | 0)
// LPENH is for pins SLCD/LP[32..51], where bit 0 represents pin 32.
#define CONF_SLCD_LPENH (\
        (uint32_t)1 << (32 - 32) | \
        (uint32_t)1 << (33 - 32) | \
        (uint32_t)1 << (34 - 32) | \
        (uint32_t)1 << (35 - 32) | \
        (uint32_t)1 << (42 - 32) | \
        (uint32_t)1 << (43 - 32) | \
        (uint32_t)1 << (48 - 32) | \
        (uint32_t)1 << (49 - 32) | \
        (uint32_t)1 << (50 - 32) | \
        (uint32_t)1 << (51 - 32) | 0)


// 9-pin connector
#define A0 GPIO(GPIO_PORTB, 4)
#define WATCH_A0_EIC_CHANNEL 4
#define A1 GPIO(GPIO_PORTB, 1)
#define WATCH_A1_EIC_CHANNEL 1
#define A2 GPIO(GPIO_PORTB, 2)
#define WATCH_A2_EIC_CHANNEL 2
#define A3 GPIO(GPIO_PORTB, 3)
#define WATCH_A3_EIC_CHANNEL 3
#define A4 GPIO(GPIO_PORTB, 0)
#define WATCH_A4_EIC_CHANNEL 0
#define SDA GPIO(GPIO_PORTB, 30)
#define SCL GPIO(GPIO_PORTB, 31)

// aliases for as A3/A4; these were mentioned as D0/D1 in early documentation.
#define D0 GPIO(GPIO_PORTB, 3)
#define D1 GPIO(GPIO_PORTB, 0)

// interrupt mapping
#define EXT_IRQ_AMOUNT 6
#define CONFIG_EIC_EXTINT_MAP {0, PIN_PB00}, {1, PIN_PB01}, {2, PIN_PA02}, {3, PIN_PB03}, {5, PIN_PB05}, {7, PIN_PA07},

#endif // PINS_H_INCLUDED

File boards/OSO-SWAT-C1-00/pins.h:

#ifndef PINS_H_INCLUDED
#define PINS_H_INCLUDED

// Detects if we are on USB power.
#define VBUS_DET GPIO(GPIO_PORTB, 5)

// Buttons
#define BTN_ALARM GPIO(GPIO_PORTA, 2)
#define WATCH_BTN_ALARM_EIC_CHANNEL 2
#define BTN_LIGHT GPIO(GPIO_PORTA, 30)
#define WATCH_BTN_LIGHT_EIC_CHANNEL 10
#define BTN_MODE GPIO(GPIO_PORTA, 31)
#define WATCH_BTN_MODE_EIC_CHANNEL 11

// Temperature Sensor
#define TS_ENABLE GPIO(GPIO_PORTB, 23)
#define TEMPSENSE GPIO(GPIO_PORTA, 3)

// Light Sensor
#define IR_ENABLE GPIO(GPIO_PORTB, 22)
#define IRSENSE GPIO(GPIO_PORTA, 4)

// Buzzer
#define BUZZER GPIO(GPIO_PORTA, 27)
#define WATCH_BUZZER_TCC_PINMUX PINMUX_PA27F_TCC0_WO5
#define WATCH_BUZZER_TCC_CHANNEL 1

// LEDs
#define WATCH_INVERT_LED_POLARITY

#define RED GPIO(GPIO_PORTA, 12)
#define WATCH_RED_TCC_CHANNEL 2
#define WATCH_RED_TCC_PINMUX PINMUX_PA12F_TCC0_WO6

#define BLUE GPIO(GPIO_PORTA, 13)
#define WATCH_BLUE_TCC_CHANNEL 3
#define WATCH_BLUE_TCC_PINMUX PINMUX_PA13F_TCC0_WO7

#define GREEN GPIO(GPIO_PORTA, 22)
#define WATCH_GREEN_TCC_CHANNEL 0
#define WATCH_GREEN_TCC_PINMUX PINMUX_PA22F_TCC0_WO4

// Segment LCD
#define SLCD0 GPIO(GPIO_PORTB, 6)
#define SLCD1 GPIO(GPIO_PORTB, 7)
#define SLCD2 GPIO(GPIO_PORTB, 8)
#define SLCD3 GPIO(GPIO_PORTB, 9)
#define SLCD4 GPIO(GPIO_PORTA, 5)
#define SLCD5 GPIO(GPIO_PORTA, 6)
#define SLCD6 GPIO(GPIO_PORTA, 7)
#define SLCD7 GPIO(GPIO_PORTA, 8)
#define SLCD8 GPIO(GPIO_PORTA, 9)
#define SLCD9 GPIO(GPIO_PORTA, 10)
#define SLCD10 GPIO(GPIO_PORTA, 11)
#define SLCD11 GPIO(GPIO_PORTB, 11)
#define SLCD12 GPIO(GPIO_PORTB, 12)
#define SLCD13 GPIO(GPIO_PORTB, 13)
#define SLCD14 GPIO(GPIO_PORTB, 14)
#define SLCD15 GPIO(GPIO_PORTB, 15)
#define SLCD16 GPIO(GPIO_PORTA, 14)
#define SLCD17 GPIO(GPIO_PORTA, 15)
#define SLCD18 GPIO(GPIO_PORTA, 16)
#define SLCD19 GPIO(GPIO_PORTA, 17)
#define SLCD20 GPIO(GPIO_PORTA, 18)
#define SLCD21 GPIO(GPIO_PORTA, 19)
#define SLCD22 GPIO(GPIO_PORTB, 16)
#define SLCD23 GPIO(GPIO_PORTB, 17)
#define SLCD24 GPIO(GPIO_PORTA, 20)
#define SLCD25 GPIO(GPIO_PORTA, 21)
#define SLCD26 GPIO(GPIO_PORTA, 23)
// This board uses a slightly different pin mapping from the standard watch, and it's not enough to
// just declare the pins. We also have to set the LCD Pin Enable register with the SLCD pins we're
// using. These numbers are not port/pin numbers, but the "SLCD/LP[x]" numbers in the pinmux table.
// If not defined in pins.h, the LCD driver will fall back to the pin mapping in hpl_slcd_config.h.
// LPENL is for pins SLCD/LP[0..31].
#define CONF_SLCD_LPENL (\
        (uint32_t)1 <<  0 | \
        (uint32_t)1 <<  1 | \
        (uint32_t)1 <<  2 | \
        (uint32_t)1 <<  3 | \
        (uint32_t)1 <<  5 | \
        (uint32_t)1 <<  6 | \
        (uint32_t)1 <<  7 | \
        (uint32_t)1 << 11 | \
        (uint32_t)1 << 12 | \
        (uint32_t)1 << 13 | \
        (uint32_t)1 << 14 | \
        (uint32_t)1 << 21 | \
        (uint32_t)1 << 22 | \
        (uint32_t)1 << 23 | \
        (uint32_t)1 << 24 | \
        (uint32_t)1 << 25 | \
        (uint32_t)1 << 30 | \
        (uint32_t)1 << 31 | 0)
// LPENH is for pins SLCD/LP[32..51], where bit 0 represents pin 32.
#define CONF_SLCD_LPENH (\
        (uint32_t)1 << (32 - 32) | \
        (uint32_t)1 << (33 - 32) | \
        (uint32_t)1 << (34 - 32) | \
        (uint32_t)1 << (35 - 32) | \
        (uint32_t)1 << (42 - 32) | \
        (uint32_t)1 << (43 - 32) | \
        (uint32_t)1 << (48 - 32) | \
        (uint32_t)1 << (49 - 32) | \
        (uint32_t)1 << (51 - 32) | 0)


// 9-pin connector
#define A0 GPIO(GPIO_PORTB, 4)
#define WATCH_A0_EIC_CHANNEL 4
#define A1 GPIO(GPIO_PORTB, 1)
#define WATCH_A1_EIC_CHANNEL 1
#define A2 GPIO(GPIO_PORTB, 2)
#define WATCH_A2_EIC_CHANNEL 2
#define A3 GPIO(GPIO_PORTB, 3)
#define WATCH_A3_EIC_CHANNEL 3
#define A4 GPIO(GPIO_PORTB, 0)
#define WATCH_A4_EIC_CHANNEL 0
#define SDA GPIO(GPIO_PORTB, 30)
#define SCL GPIO(GPIO_PORTB, 31)

// aliases for as A3/A4; these were mentioned as D0/D1 in early documentation.
#define D0 GPIO(GPIO_PORTB, 3)
#define D1 GPIO(GPIO_PORTB, 0)

// interrupt mapping
#define EXT_IRQ_AMOUNT 6
#define CONFIG_EIC_EXTINT_MAP {0, PIN_PB00}, {1, PIN_PB01}, {2, PIN_PA02}, {3, PIN_PB03}, {10, PIN_PA30}, {11, PIN_PA31},

#endif // PINS_H_INCLUDED

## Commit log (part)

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2024-08-24 Additional code review change
2024-08-24 properly refactored
2024-08-24 updating the keggings_face.h usage documentation
2024-08-24 removed randonaut_face from movement_face.h
2024-08-27 Comment change
2024-08-28 refactor and more EVENT reactions
2024-08-28 style: remove extra whitespace
2024-08-30 wait for RTC SYNCBUSY in watch_register_extwake_callback
2024-08-30 my customizations: preset alarms and timezone
2024-08-30 refactored but still debugging enabled
2024-08-31 square root skips entering second number
2024-08-31 forgot to mention long press MODE for next face
2024-08-31 fix build warnings
2024-08-31 removed note about mode long press
2024-08-31 commented out simple_calculator_face debugging
2024-08-31 negative toggle was only for first_num -- fixed
2024-09-01 mode long press = reset_all()
2024-09-01 adding recent simple_calc changes
2024-09-02 Require long press on alarm to modify prefs
2024-09-02 comment out debugging in simple_calc_face
2024-09-03 sleep light function
2024-09-03 Don't allow readding already guessed items
2024-09-03 Able to turn the expanded dict on and off with a variable
2024-09-03 Added fast cycle
2024-09-03 Another fix on the word_check
2024-09-03 Start of Wordle
2024-09-03 bug fix on max score
2024-09-03 Swapped button mapping and removed fast iteration
2024-09-03 hard mode btn changed; logic changed on daily streak so if puzzle wasn't started and completed the previous day, then drop the streak
2024-09-03 WORDLE_USE_DAILY_STREAK logic changed
2024-09-03 LAP indicator now dispalys on all screens
2024-09-03 Changed size of word lists from const int to #define to avoid folding constant array error
2024-09-03 Fix on playing with daily streak
2024-09-03 Fixed leaving the screen and coming back
2024-09-03 modified Wordle list to use Wordle's own list and add 2 more letters
2024-09-03 skip_wrong_letter is now a toggle
2024-09-03 Streak face fix
2024-09-03 Added ability to find best starting word
2024-09-03 Reset streak if don't continue
2024-09-03 Readding comment showing count of possible words.
2024-09-03 Added continue screen
2024-09-03 Added ability to guess non-dict words and repeats as that can save 11.5KB of watch memory
2024-09-03 bug fix on displaying time in LE mode
2024-09-03 Added baby mode which used to be easy mode; easy mode is now same speed as normal, but 3 frames to jump and normal is 2 frames.
2024-09-03 Gave an extra jumping frame for non-hard mode; Curr scroll now loops; Title changed to ER
2024-09-03 Reformat to remove some hardocded variables
2024-09-03 Added author in header
2024-09-03 hi score resets weekly
2024-09-03 Modified hi score display to allow for 3 digits in hi-score, it now resets at the beginning of each month
2024-09-03 Reduced struct memory per code review
2024-09-03 Call set_time_face on long press of alarm. Move alert toggle to light.
2024-09-03 Made the inputs for the DATE option be text, not numbers.
2024-09-03 Added ability to make default time on the watch be PC clock's during compilation
2024-09-03 Added check for if not using Linux; renamed defines
2024-09-03 Fixed typo in author name
2024-09-03 Added requirements.txt; Added ability to not need Spotify credentials and ignore getting popularity scores.
2024-09-03 Added times where chiming does not occur
2024-09-04 bump to the newer upload-artifact github action
2024-09-05 add metal gear solid codec tune
2024-09-06 add the ability to set location and birthdate in movement config
2024-09-06 Made the T and Y characters look more unique on the 4 and 6 position
2024-09-06 Delay for starting the debounce no loonger happens
2024-09-06 using cb_fast_tick again
2024-09-06 Made the debounce register rising edges rather than falling edges
2024-09-06 debouince now uses cb_fast_tick and holding the button now also gets debounced
2024-09-06 A little bit of clean-up
2024-09-06 Changed debounce to ignore button presses after a press down or up rathe rthan dact after a set amount of time due to an issue of delay_ms allowing a shoft-bricking
2024-09-06 Code review edits
2024-09-06 fix: july has 31 days
2024-09-06 avoid delta overflow in countdown draw
2024-09-06 Fix to remove compiler complaint
2024-09-06 Typo fix on PREFERENCES_FACE_NUM_PREFERENCES
2024-09-06 add temp input to simulator
2024-09-07 Added ability for the simple_clock_face to use sunrise or sunset as the time to turn the hourly beep on or off
2024-09-07 No longer run full sunrise logic if hourly_chime_always is set
2024-09-07 display closest deadline on activation
2024-09-07 removed higher frequency in first loop run.
2024-09-07 Made cards go through a deck format.
2024-09-07 support for alarm
2024-09-08 add blinking to DST toggle in settings page
2024-09-08 Tally face sound now uses the preference's beep so decrementing fast can happen immedietly
2024-09-08 make: fix missing separator error
2024-09-08 faces/tally: add yugioh life point presets
    Add common Yu-Gi-Oh card game life point preset values
    for the tally face, opt in by defining a preprocessor macro.
2024-09-08 faces/tally: convert size into compile time const
    Creates a macro that returns the size of the presets array,
    converting it into a compile time constant value that occupies
    no memory and that compilers can constant fold into other expressions
    potentially leading to dead code elimination.
2024-09-08 Daylight offsets now references the timezone of the destination; but it does cause an issue due to DST
2024-09-08 sunrise sunset fix during DST
2024-09-10 Gave same treatment to timer_face
2024-09-10 Made the watch pull from backup on wake
2024-09-10 If the sunrise function does not run correctly, then don't chime
2024-09-10 Revert PR #387 - fixes LE state restoration
    This commit caused state restored from backup registers
    to be overwritten. It is thereby reverted until a better
    solution is found or movement is refactored.
    This reverts commit 524098b9258232964d7756d4d44f16b006d340bf.
    Reviewed-by: Matheus Afonso Martins Moreira <matheus@matheusmoreira.com>
    References: https://github.com/joeycastillo/Sensor-Watch/pull/474
2024-09-16 faces/alarm: fix 24h indication in 024h mode
    The watch was not indicating to the user that it was in 24h mode
    when set to the leading zero 024h time format. This could lead
    to ambiguity and confusion, so make sure to indicate 24h mode.
    Closes #476.
    Reported-by: CarpeNoctem <cryptomax@pm.me>
    GitHub-Issue: https://github.com/joeycastillo/Sensor-Watch/issues/476
2024-09-16 faces/simple_clock: clear segments if not in 024h
    There was an issue where the simple clock's display would remain in
    024h mode even after switching back to 12h/24h mode because it only
    took into account the leading zero bit, whose value is meaningless
    unless the 24h mode bit is also set.
    The issue is fixed by taking both bits into account.
    Closes #476.
2024-09-16 Reset debounce values on wake; avoid sleeping when debounce occurring; Clean up with _reset_debounce_ticks
2024-09-17 Revert PR #470 - implement automatic DST toggling
    The DST code has not yet been fully tested, the upcoming movement
    refactor is upon us and it will integrate with the micro timezone
    library anyway. Revert it so that next can be merged into main.
    This reverts commit ac5bf8cfce67cdb5662aeea618c2eb9511f0d190, reversing
    changes made to 5a8a49a8c77d6d5ba0f46f0e5b51dec2daba46db.
2024-09-17 Revert PR #470 - fixes world_clock2 face
    The DST code has not yet been fully tested, the upcoming movement
    refactor is upon us and it will integrate with the micro timezone
    library anyway. Revert it so that next can be merged into main.
    This reverts commit 3c86a42aa83356735be2bd84b7027b156e8d3a2c, reversing
    changes made to be969c4deb144280b59d0293cc45dc3443b096cf.
2024-09-18 silence warning in beeps_face
2024-09-18 remove menstrual_cycle_face from default list
2024-09-18 beep when cpu is done computing a move
2024-09-18 use SCL_Game->ply instead of board[ply_byte]
2024-09-18 smallchess: fix compile warnings
2024-09-18 fix warnings
2024-09-18 silence warnings in metronome_face
2024-09-18 Metronome Complication (#303)
    * Metronome Complication
    A simple metronome complication that allows user to set BPM, toggle sound, and set counts per measure.
    * silence warnings in metronome_face
    * avoid mode button in metronome settings, other tweaks
    ---------
2024-09-18 Add Butterfly game face (#338)
2024-09-18 silence warnings in butterfly_game_face
2024-09-21 Fixed quirk from directly casting lat into double where time offset is double UT
2024-09-28 Add Chirpy support to databank
2024-10-16 original sunrise_sunset_face.h
2024-10-16 and all the other adjustments
2024-10-17 While likely unneeded now, I readded the logic to change the birthday from 0 to 1 in day_one_face as that's how it was before I began touching it
2024-10-18 Most people probably don't want my preset
2024-10-19 Removing my preset (again)
2024-10-21 smaller int range for memory stack
2024-11-04 Update beer_counter_face.c
    Updated Code to use Seidl et al. approach which takes height into consideration and calculates bac more exactly.
    Also added BMI calculator so values too low/high throw an error.
2024-11-05 Update beer_counter_face.h
    added an explicit disclaimer to not fully rely on the calculations of this watchface
2024-11-05 Update beer_counter_face.h
    changed ST screen to TTS (time to sobriety) because of the possibility of confusing it with stopwatch (ST)
2024-11-06 Update beer_counter_face.c
    updated code to properly calculate BAC when incrementing beer-counter and also time to sobriety
2024-11-06 Update beer_counter_face.c
    added support for modifying volume of drink and alcohol content of drink
2024-11-10 Lander face
    My version of a standard planet landing game.
    Nuisances includes heroism, pilot ratings, injury calculations and hamsters with attitudes.
2024-11-13 Added a simple streak counter. This let's you check off an activity everyday and counts the consecutive days that you've completed it. It also has a counter for the highest streak accomplished.
2025-03-08 Sensor Watch Pro
2025-03-12 feature merge commit and PR cleanup/documentation
2025-03-29 Artist names now scroll
2025-03-29 Popularity score includes monthly listeners and manually confirmed each artist on Spotify.
2025-04-01 Add links to schematics and gerbers for different models
2025-04-02 Implement daylight saving toggle for world clock face2
    - Added functionality to toggle daylight saving time for the current time zone using a long press on the ALARM button.
    - Updated the display logic to show the lap indicator based on daylight saving status.
    - Enhanced documentation to reflect the new behavior.
2025-04-15 Remove unused variable
2025-05-07 sensor watch pro test procedure
2025-05-16 final test script for Pro
2025-05-19 Updated array to new Lolla schedule
2025-05-21 Renamed the enums
2025-05-21 Fixes after enum testing
2025-05-22 Festival update less often and scroll to no act on day shows no act
2025-05-22 Don't jump to title on activate
2025-06-18 Cycling act info won't jump to title
2025-06-22 Moved utils to a snake case folder
2025-07-26 Added documentation on face usage
2025-07-26 Moved to using more updated Clashfinder schedule; Ordered stages based on popularity
2025-07-26 Undid last commit
2025-08-06 Changed some lettering
2025-08-27 Tick colon on custom display when displaying time
2025-08-31 Time display updates on any prime number.
    Simple watch display updates on any second where the total 5 or 6 digit displayed number is prime.
    This version supports only 12 hour clocks are requires less memory than it's full sized counterpart.
2025-08-31 Prime Number Hunter Safari
    Press left button for prime numbers, right for composite.
    Earn croutons to go on safari and hunt the big game prime numbers.
    Big game numbers permanently improve your high score list.**
    There is no time limit on a safari.
    Advance to larger targets and new venues as your three big game trophy numbers improve.
    You may override the auto-selected starting level at the beginning

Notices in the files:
PCB/Main Boards/OSO-SWAT-A1/OSO-SWAT-A1-05.brd:
CC-BY-SA 4.0
parts and their libraries:
microbuilder: This work is placed in the public domain, and may be freely used for commercial and non-commercial work with the following conditions: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
COPYRIGHT: Copyright (C) 2018 Accelerated Designs. All rights reserved
